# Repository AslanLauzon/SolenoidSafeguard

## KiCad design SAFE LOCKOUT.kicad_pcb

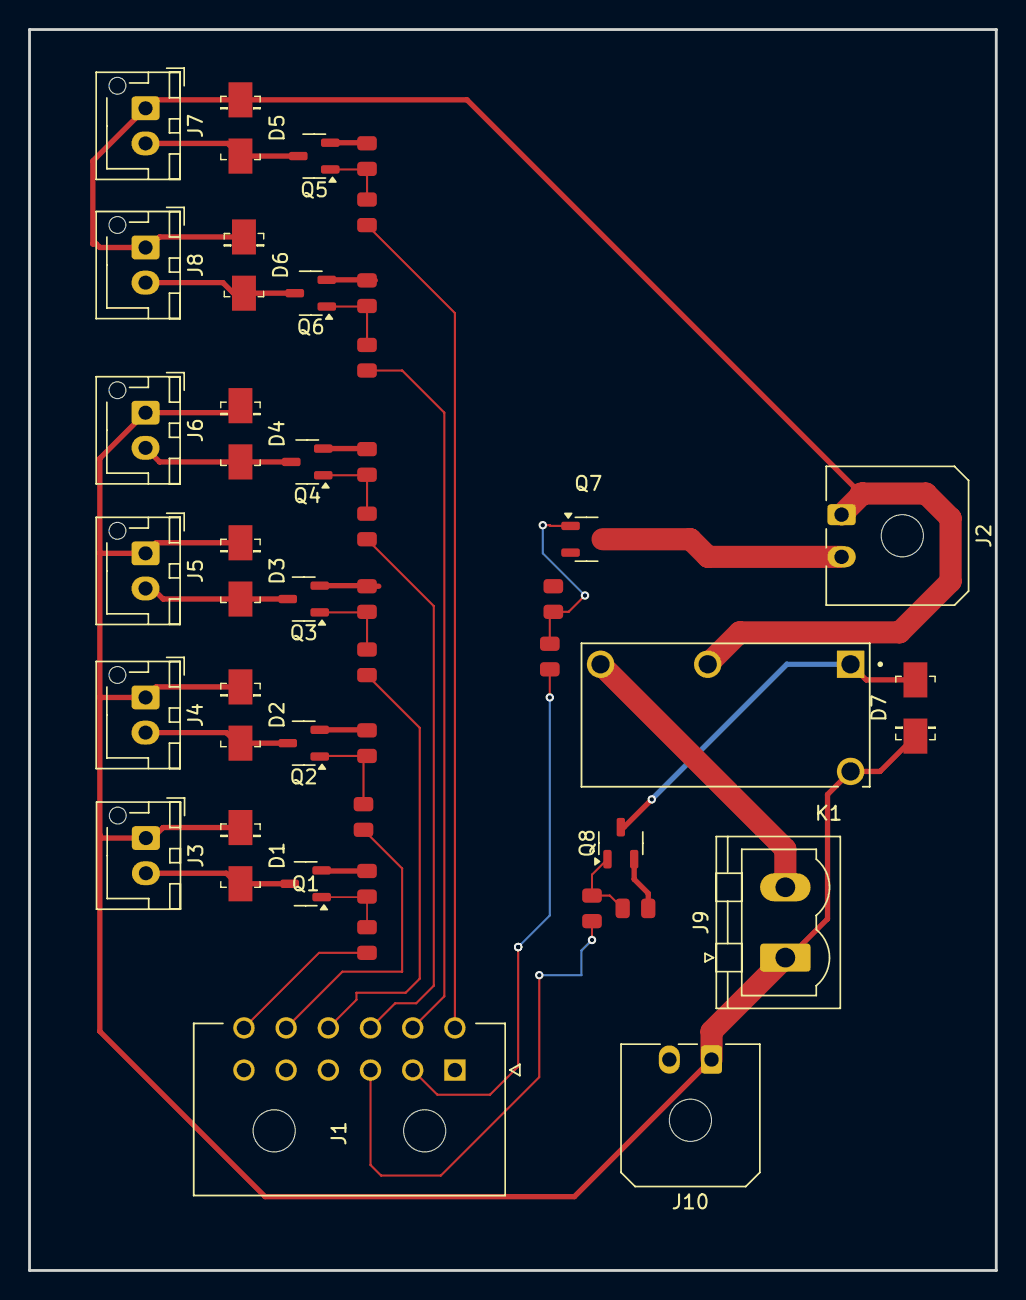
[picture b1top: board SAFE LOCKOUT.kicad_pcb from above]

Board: 2 copper layers, 68.8 x 88.2 mm, 42 parts (0 on the bottom side), 28 nets.

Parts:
D1, D2, D3, D4, D5, D6, D7: SS14; DO-214AC
J1: Conn_01x12_Pin; MOLEX_430451200
J2, J10: Conn_01x02_Pin; Molex_Micro-Fit_3.0_43650-0200_1x02_P3.00mm_Horizontal
J3, J4, J5, J6, J7, J8: Conn_01x02_Pin; JST_XH_B2B-XH-AM_1x02_P2.50mm_Vertical
J9: Conn_01x02_Pin; PhoenixContact_MSTBVA_2,5_2-G_1x02_P5.00mm_Vertical
K1: PR30-24V-450-1A; RELAY_PR30-24V-450-1A
Q1, Q2, Q3, Q4, Q5, Q6, Q7, Q8: BSS138; SOT-23-3
R1, R3, R5, R7, R9, R11, R13, R15: R100; R_0805
R2, R4, R6, R8, R10, R12, R16: 100KR; R_0805
R14: R100K; R_0805

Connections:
+24V: D1.K, D2.K, D3.K, D4.K, D7.K, J3.1, J4.1, J5.1, J6.1, J9.1, J10.1, K1.16
AV RUN CTL: J1.8, R11.1
AV FILL CTL: J1.7, R9.1
AV FILL VLV: D5.A, J7.2, Q5.3 (D)
AV RUN VLV: D6.A, J8.2, Q6.3 (D)
GND: J1.1, J10.2, Q1.2 (S), Q2.2 (S), Q3.2 (S), Q4.2 (S), Q5.2 (S), Q6.2 (S), Q7.2 (S), Q8.2 (S), R2.1, R4.1, R6.1, R8.1, R10.1, R12.1, R14.1, R16.1
IGNITOR 3A -: J2.2, Q7.3 (D)
IGNITOR CTL: J1.2, R13.1
unnamed: J9.2, K1.8
unnamed: Q1.1 (G), R1.2, R2.2
unnamed: Q2.1 (G), R3.2, R4.2
unnamed: Q3.1 (G), R5.2, R6.2
unnamed: Q4.1 (G), R7.2, R8.2
unnamed: Q5.1 (G), R9.2, R10.2
unnamed: Q6.1 (G), R11.2, R12.2
unnamed: Q7.1 (G), R13.2, R14.2
unnamed: D7.A, K1.1, Q8.3 (D)
unnamed: Q8.1 (G), R15.2, R16.2
RELAY SFEGRD CTL: J1.3, R15.1
SAFE POWER 24v: D5.K, D6.K, J2.1, J7.1, J8.1, K1.5
VLV 1: D1.A, J3.2, Q1.3 (D)
VLV 1 CTL: J1.12, R1.1
VLV 2: D2.A, J4.2, Q2.3 (D)
VLV 2 CTL: J1.11, R3.1
VLV 3: D3.A, J5.2, Q3.3 (D)
VLV 3 CTL: J1.10, R5.1
VLV 4: D4.A, J6.2, Q4.3 (D)
VLV 4 CTL: J1.9, R7.1

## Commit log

2025-07-15 changed power source and footprints
2025-07-15 changed screw terminal
2025-07-16 added pcb footprints
2025-07-16 added footprints to repo
2025-07-19 logan did pcb, some suff still needs to be fixed
